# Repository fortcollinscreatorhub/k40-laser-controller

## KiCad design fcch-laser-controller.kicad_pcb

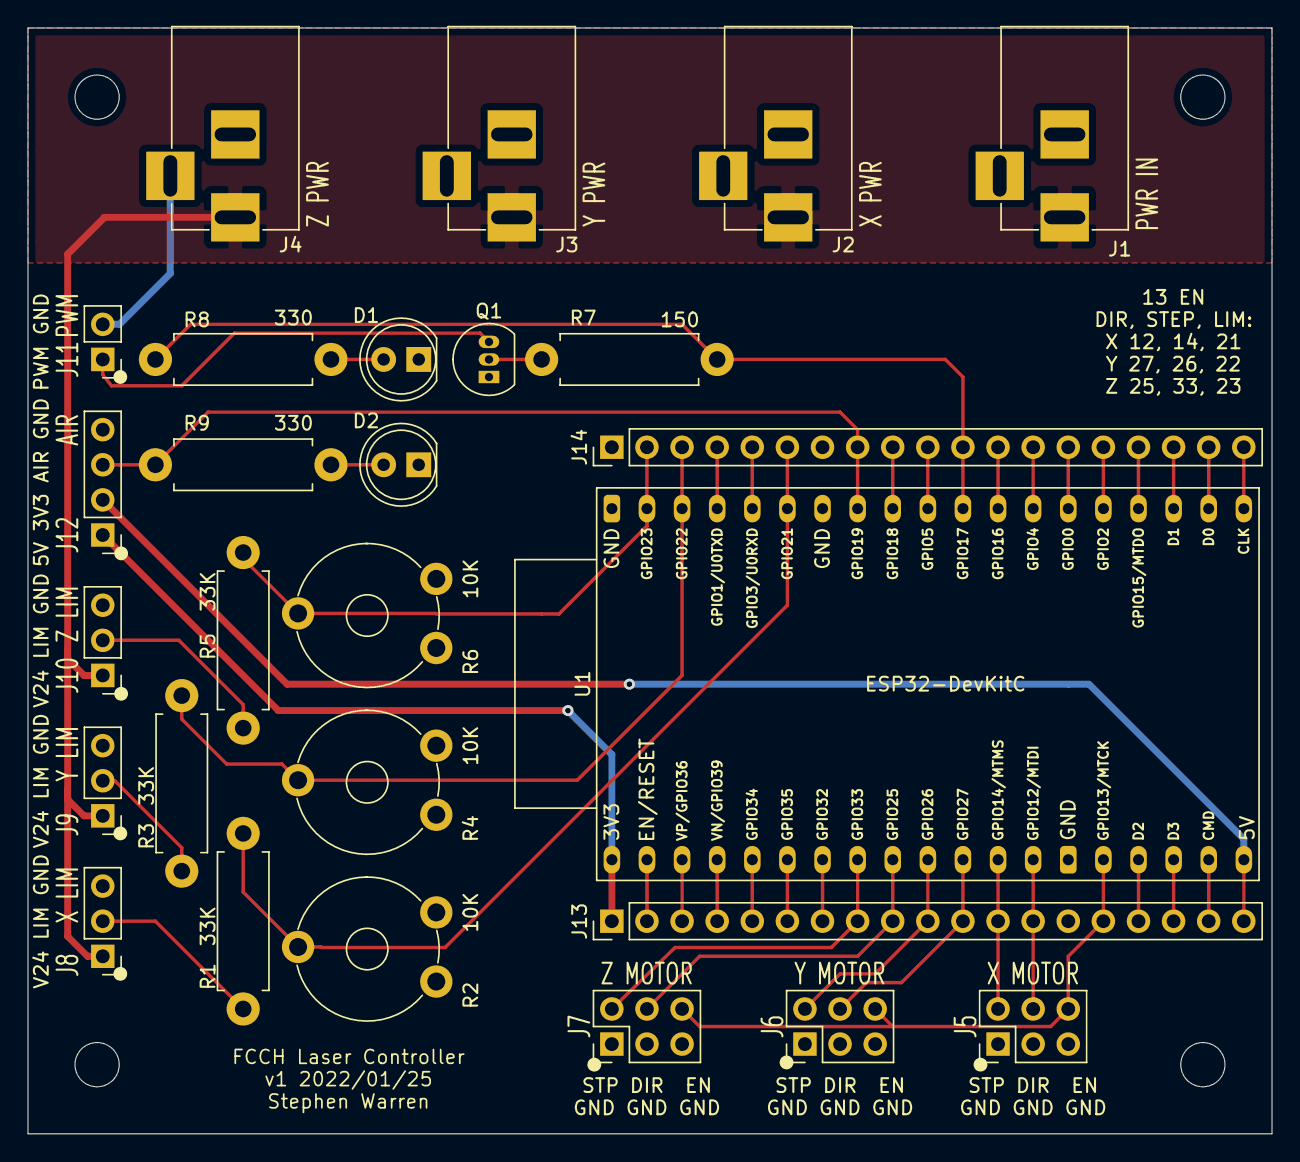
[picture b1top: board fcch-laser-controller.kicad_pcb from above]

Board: 2 copper layers, 90.0 x 80.0 mm, 31 parts (0 on the bottom side), 44 nets.

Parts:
D1, D2: LED; LED_D5.0mm
H1, H2, H3, H4: MountingHole; MountingHole_3.2mm_M3
J1, J2, J3, J4: Barrel_Jack_Switch; BARREL_JACK
J5, J6, J7: Conn_02x03_Odd_Even; Pin_Header_Straight_2x03_Pitch2.54mm
J8, J9, J10: Conn_01x03_Male; Pin_Header_Straight_1x03_Pitch2.54mm
J11: Conn_01x02_Male; Pin_Header_Straight_1x02_Pitch2.54mm
J12: Conn_01x04_Male; Pin_Header_Straight_1x04_Pitch2.54mm
J13, J14: Conn_01x19_Male; Pin_Header_Straight_1x19_Pitch2.54mm
Q1: PN2222A; TO-92_Inline_Narrow_Oval
R1, R3, R5: 33K; R_Axial_DIN0411_L9.9mm_D3.6mm_P12.70mm_Horizontal
R2, R4, R6: 10K; Potentiometer_Trimmer_Piher_PT-10v10_Horizontal_Px10.0mm_Py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
R7: 150; R_Axial_DIN0411_L9.9mm_D3.6mm_P12.70mm_Horizontal
R8, R9: 330; R_Axial_DIN0411_L9.9mm_D3.6mm_P12.70mm_Horizontal
U1: ESP32-DevKitC

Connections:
/AIR: J12.3, J14.8, R9.1, U1.31
/GND: D1.1, D2.1, J1.2, J1.3, J2.2, J2.3, J3.2, J3.3, J4.2, J4.3, J5.1, J5.3, J5.5, J6.1, J6.3, J6.5, J7.1, J7.3, J7.5, J8.3, J9.3, J10.3, J11.2, J12.4, J13.14, J14.1, J14.7, Q1.1, R2.3, R4.3, R6.3, U1.14, U1.32, U1.38
/PWM: J14.11, R7.1, R8.1, U1.28
/PWMOC: J11.1, Q1.3
/V3_3: J12.1, J13.1, U1.1
/V5: J12.2, J13.19, U1.19
/V24: J1.1, J2.1, J3.1, J4.1, J8.1, J9.1, J10.1
/XDIR: J5.4, J13.13, U1.13
/XEN: J5.6, J6.6, J7.6, J13.15, U1.15
/XLIM: J14.6, R1.2, R2.2, U1.33
/XLIM24: J8.2, R1.1
/XSTEP: J5.2, J13.12, U1.12
/YDIR: J6.4, J13.11, U1.11
/YLIM: J14.3, R3.2, R4.2, U1.36
/YLIM24: J9.2, R3.1
/YSTEP: J6.2, J13.10, U1.10
/ZDIR: J7.4, J13.9, U1.9
/ZLIM: J14.2, R5.2, R6.2, U1.37
/ZLIM24: J10.2, R5.1
/ZSTEP: J7.2, J13.8, U1.8
unnamed: D1.2, R8.2
unnamed: D2.2, R9.2
unnamed: J13.2, U1.2
unnamed: J13.3, U1.3
unnamed: J13.4, U1.4
unnamed: J13.5, U1.5
unnamed: J13.6, U1.6
unnamed: J13.7, U1.7
unnamed: J13.16, U1.16
unnamed: J13.17, U1.17
unnamed: J13.18, U1.18
unnamed: J14.4, U1.35
unnamed: J14.5, U1.34
unnamed: J14.9, U1.30
unnamed: J14.10, U1.29
unnamed: J14.12, U1.27
unnamed: J14.13, U1.26
unnamed: J14.14, U1.25
unnamed: J14.15, U1.24
unnamed: J14.16, U1.23
unnamed: J14.17, U1.22
unnamed: J14.18, U1.21
unnamed: J14.19, U1.20
unnamed: Q1.2, R7.2

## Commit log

2022-01-27 Add v1-20210125 files
2022-01-27 PCB: improve 3D model situation
    - Update all 3D model filenames to match what the model paths provided in
    Ubuntu 20.04 (kicad-packages3d 5.1.5-1)
    - Some models are bogus:
    - DC jack is something similar, but not the right one.
    - Potentiometer/trimmer is something similar, but not the right one.
    - ESP32 devkit uses the pin socket that it will plug into, but that
2022-01-29 sch: fix trimmer pot part number
2022-01-29 pcb: use commas for labels
    This takes up less space, leaving slightly larger gaps between the labels
    for adjacent connectors.
2022-02-04 Add TODO list
2022-02-13 pcb: move to sub-directory
2022-02-15 Add mounting sheet
    The PCBs will mount to this, and it will mount to the chassis.
2022-02-26 pcb: enhance PCB silk, add TODO entry
    - Document the LASER and air control GPIO numbers.
    - Note that the transistor footprint may need to be changed.
2022-02-26 pcb: add one more TODO
2022-02-26 Add original grbl code
2022-02-26 grbl: add FCCH modifications
2022-02-26 Add grbl EEPROM backups
